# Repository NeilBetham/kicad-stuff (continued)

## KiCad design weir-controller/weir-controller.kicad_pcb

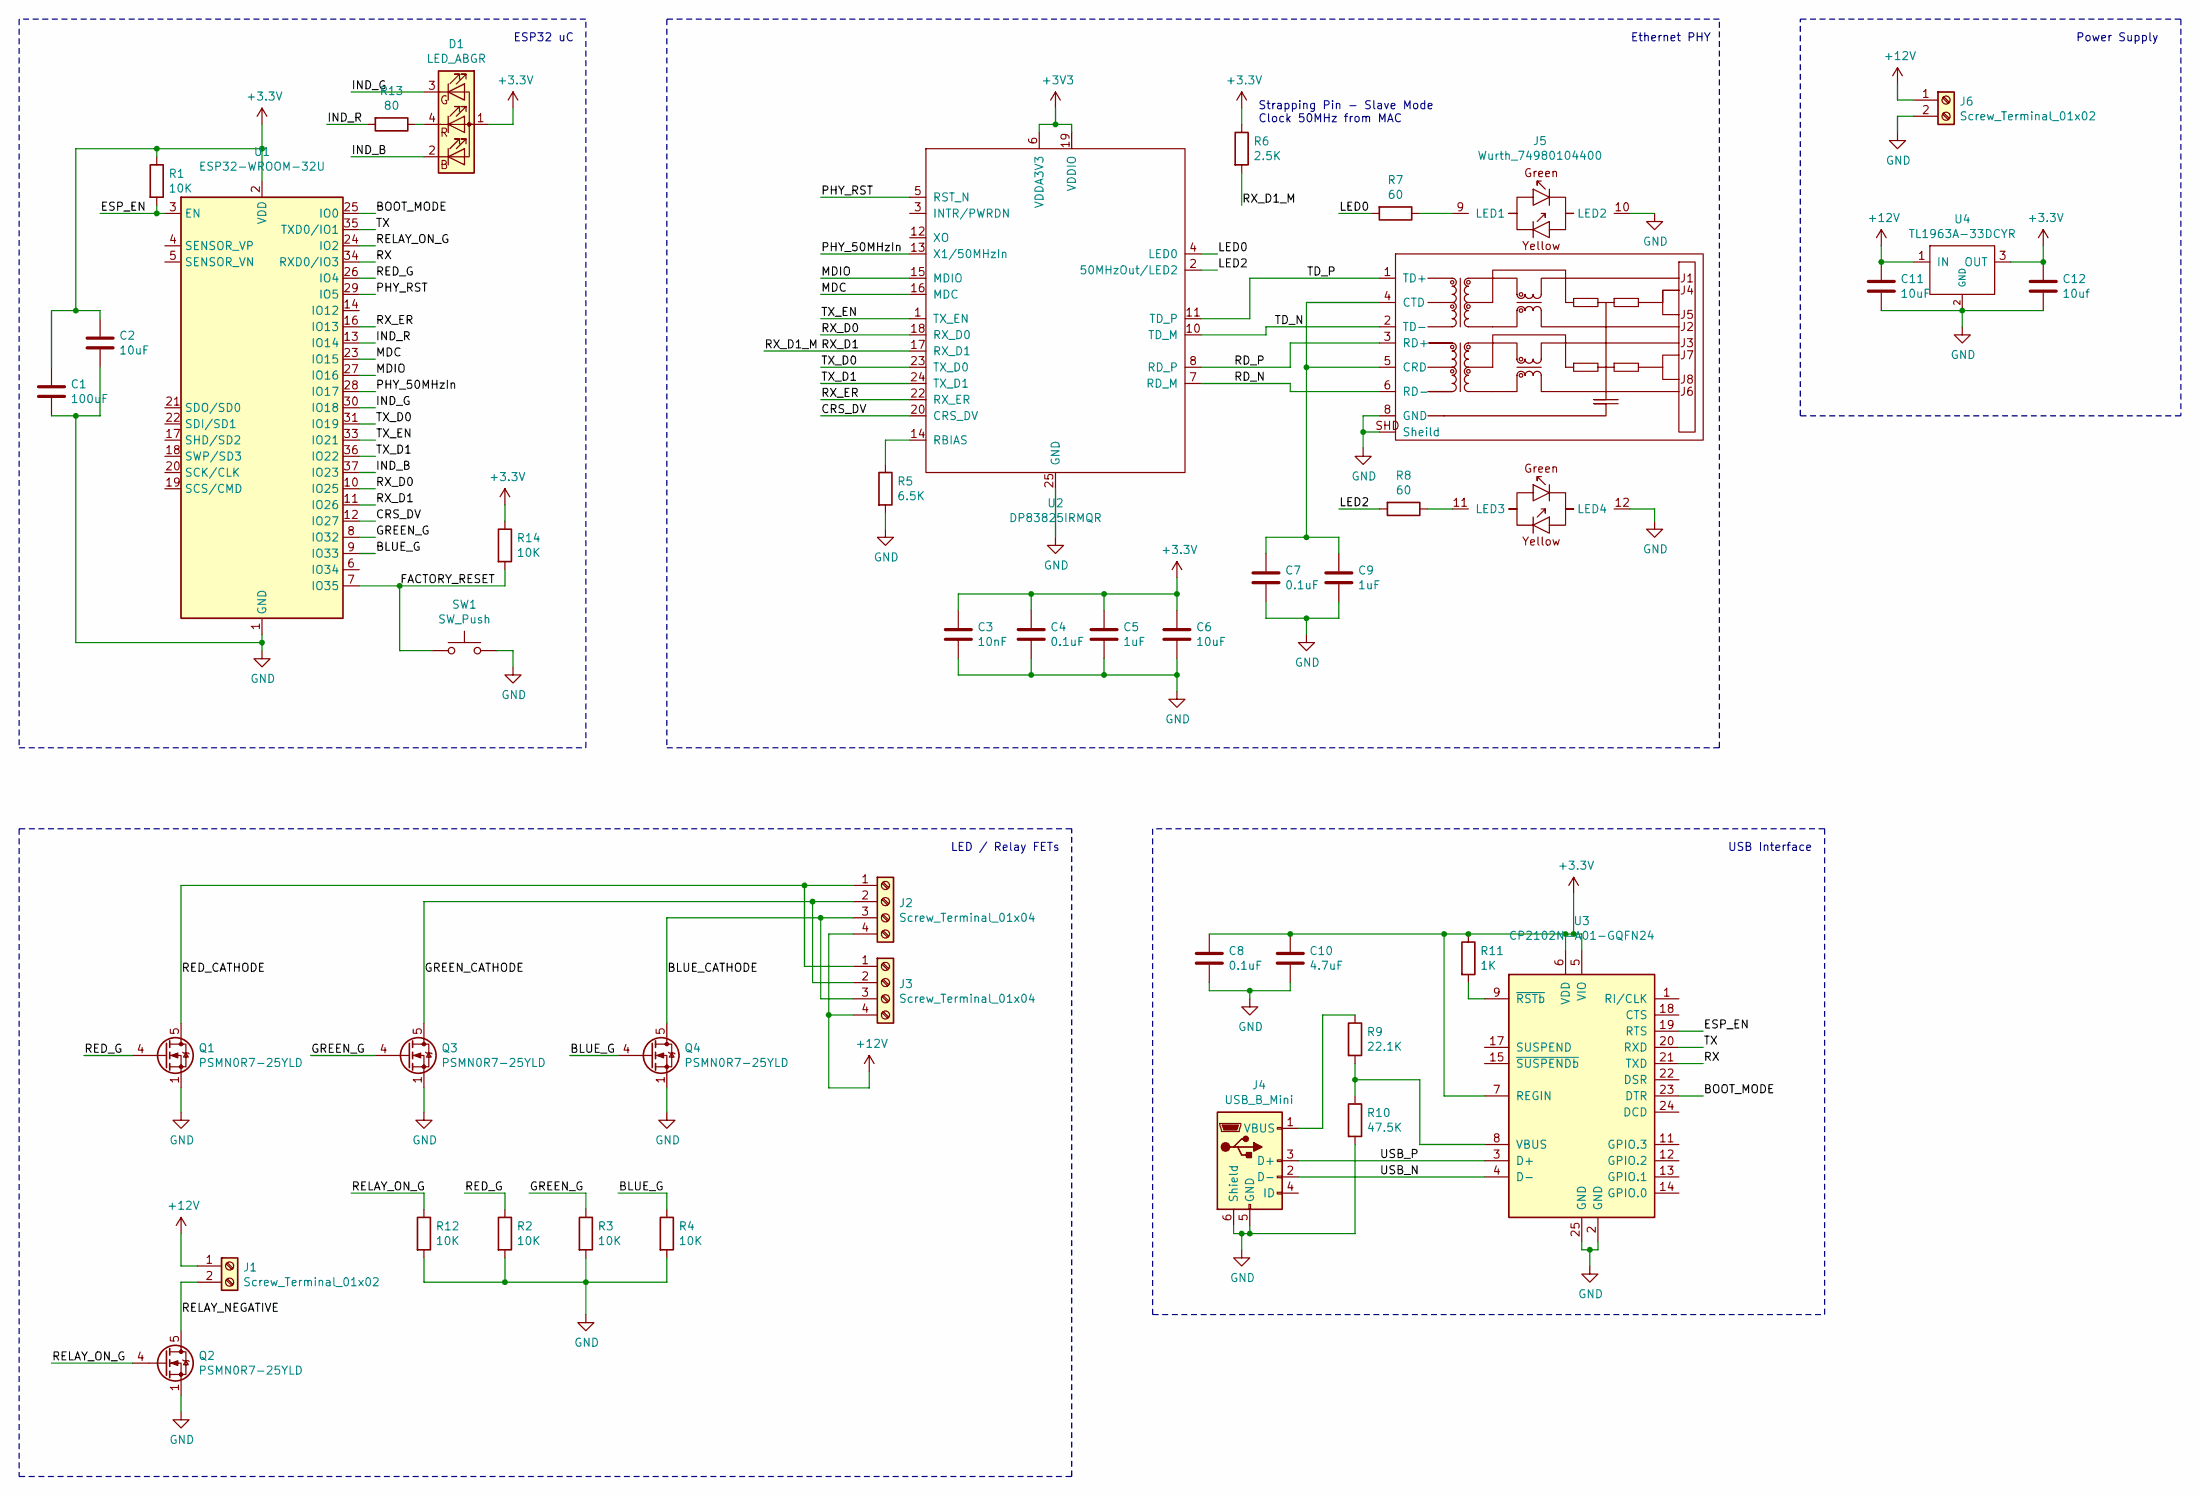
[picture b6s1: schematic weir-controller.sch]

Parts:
C1: 100uF; C_1206_3216Metric_Pad1.42x1.75mm_HandSolder
C2, C6, C11: 10uF; C_0805_2012Metric_Pad1.15x1.40mm_HandSolder
C3: 10nF; C_0805_2012Metric_Pad1.15x1.40mm_HandSolder
C4, C7, C8: 0.1uF; C_0805_2012Metric_Pad1.15x1.40mm_HandSolder
C5, C9: 1uF; C_0805_2012Metric_Pad1.15x1.40mm_HandSolder
C10: 4.7uF; C_0805_2012Metric_Pad1.15x1.40mm_HandSolder
C12: 10uf; C_0805_2012Metric_Pad1.15x1.40mm_HandSolder
D1: LED_ABGR; LED_Cree-PLCC4_2x2mm_CW
J1: Screw_Terminal_01x02; PhoenixContact_PTSA_2Pin
J2, J3: Screw_Terminal_01x04; PhoenixContact PTSA 4Pin
J4: USB_B_Mini; 54819-0589
J5: Wurth_74980104400
J6: Screw_Terminal_01x02; PhoenixContact_PTSA_2PIN_8A
Q1, Q2, Q3, Q4: PSMN0R7-25YLD; LFPAK56
R1, R2, R3, R4, R12: 10K; R_0805_2012Metric_Pad1.15x1.40mm_HandSolder
R5: 6.5K; R_0805_2012Metric_Pad1.15x1.40mm_HandSolder
R6: 2.5K; R_0805_2012Metric_Pad1.15x1.40mm_HandSolder
R7, R8: 60; R_0805_2012Metric_Pad1.15x1.40mm_HandSolder
R9: 22.1K; R_0805_2012Metric_Pad1.15x1.40mm_HandSolder
R10: 47.5K; R_0805_2012Metric_Pad1.15x1.40mm_HandSolder
R11: 1K; R_0805_2012Metric_Pad1.15x1.40mm_HandSolder
R13: 80; R_0805_2012Metric_Pad1.15x1.40mm_HandSolder
R14: 10K; R_0805_2012Metric_Pad1.20x1.40mm_HandSolder
SW1: SW_Push; PTS636
U1: ESP32-WROOM-32U
U2: DP83825IRMQR; TI_RMQ0024A
U3: CP2102N-A01-GQFN24; QFN-24-1EP_4x4mm_P0.5mm_EP2.6x2.6mm_ThermalVias
U4: TL1963A-33DCYR; SOT-223-3_TabPin2

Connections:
+12V: C11.1, J1.1, J2.4, J3.4, J6.1, U4.1 (IN)
/BLUE_CATHODE: J2.3, J3.3, Q4.5 (D)
/BLUE_G: Q4.4 (G), R4.1, U1.9 (IO33)
/BOOT_MODE: U1.25 (IO0), U3.23 (DTR)
/CRS_DV: U1.12 (IO27), U2.20 (CRS_DV)
/ESP_EN: R1.2, U1.3 (EN), U3.19 (RTS)
/FACTORY_RESET: R14.2, SW1.1, U1.7 (IO35)
/GREEN_CATHODE: J2.2, J3.2, Q3.5 (D)
/GREEN_G: Q3.4 (G), R3.1, U1.8 (IO32)
/IND_B: D1.2 (BK), U1.37 (IO23)
/IND_G: D1.3 (GK), U1.30 (IO18)
/IND_R: R13.2, U1.13 (IO14)
/LED0: R7.2, U2.4 (LED0)
/LED2: R8.2, U2.2 (50MHzOut/LED2)
/MDC: U1.23 (IO15), U2.16 (MDC)
/MDIO: U1.27 (IO16), U2.15 (MDIO)
/PHY_50MHzIn: U1.28 (IO17), U2.13 (X1/50MHzIn)
/PHY_RST: U1.29 (IO5), U2.5 (RST_N)
/RD_N: J5.6 (RD-), U2.7 (RD_M)
/RD_P: J5.3 (RD+), U2.8 (RD_P)
/RED_CATHODE: J2.1, J3.1, Q1.5 (D)
/RED_G: Q1.4 (G), R2.1, U1.26 (IO4)
/RELAY_NEGATIVE: J1.2, Q2.5 (D)
/RELAY_ON_G: Q2.4 (G), R12.1, U1.24 (IO2)
/RX: U1.34 (RXD0/IO3), U3.21 (TXD)
/RX_D0: U1.10 (IO25), U2.18 (RX_D0)
/RX_D1: R6.2, U1.11 (IO26), U2.17 (RX_D1)
/RX_ER: U1.16 (IO13), U2.22 (RX_ER)
/TD_N: J5.2 (TD-), U2.10 (TD_M)
/TD_P: J5.1 (TD+), U2.11 (TD_P)
/TX: U1.35 (TXD0/IO1), U3.20 (RXD)
/TX_D0: U1.31 (IO19), U2.23 (TX_D0)
/TX_D1: U1.36 (IO22), U2.24 (TX_D1)
/TX_EN: U1.33 (IO21), U2.1 (TX_EN)
/USB_N: J4.2 (D-), U3.4 (D-)
/USB_P: J4.3 (D+), U3.3 (D+)
GND: C1.2, C2.2, C3.2, C4.2, C5.2, C6.2, C7.2, C8.2, C9.2, C10.2, C11.2, C12.2, J4.5 (GND), J4.6 (Shield), J5.8 (GND), J5.10 (LED2), J5.12 (LED4), J5.SHD (Sheild), J6.2, Q1.1 (S), Q1.2 (S), Q1.3 (S), Q2.1 (S), Q2.2 (S), Q2.3 (S), Q3.1 (S), Q3.2 (S), Q3.3 (S), Q4.1 (S), Q4.2 (S), Q4.3 (S), R2.2, R3.2, R4.2, R5.2, R10.2, R12.2, SW1.2, U1.1 (GND), U1.15 (GND), U1.38 (GND), U1.39 (GND), U2.9 (GND), U2.21 (GND), U2.25 (GND), U3.2 (GND), U3.25 (GND), U4.2 (GND)
unnamed: C7.1, C9.1, J5.4 (CTD), J5.5 (CRD)
unnamed: D1.4 (RK), R13.1
unnamed: J4.1 (VBUS), R9.1
unnamed: J5.9 (LED1), R7.1
unnamed: J5.11 (LED3), R8.1
unnamed: R5.1, U2.14 (RBIAS)
unnamed: R9.2, R10.1, U3.8 (VBUS)
unnamed: R11.2, U3.9 (~RSTb)

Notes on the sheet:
Power Supply
USB Interface
LED / Relay FETs
Strapping Pin - Slave Mode Clock 50MHz from MAC
Ethernet PHY
ESP32 uC

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
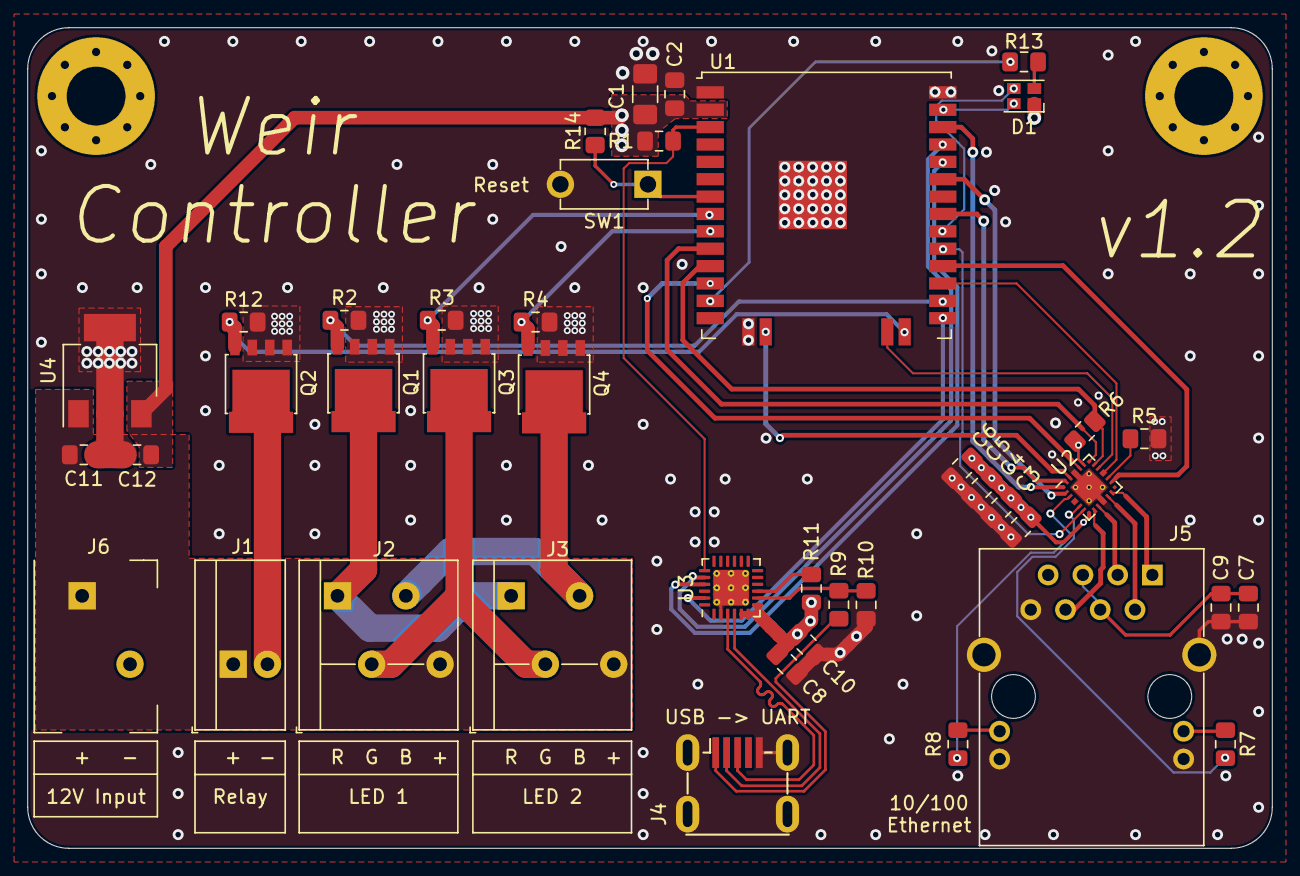
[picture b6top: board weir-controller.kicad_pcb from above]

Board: 4 copper layers, 91.0 x 60.0 mm, 42 parts (0 on the bottom side), 46 nets.

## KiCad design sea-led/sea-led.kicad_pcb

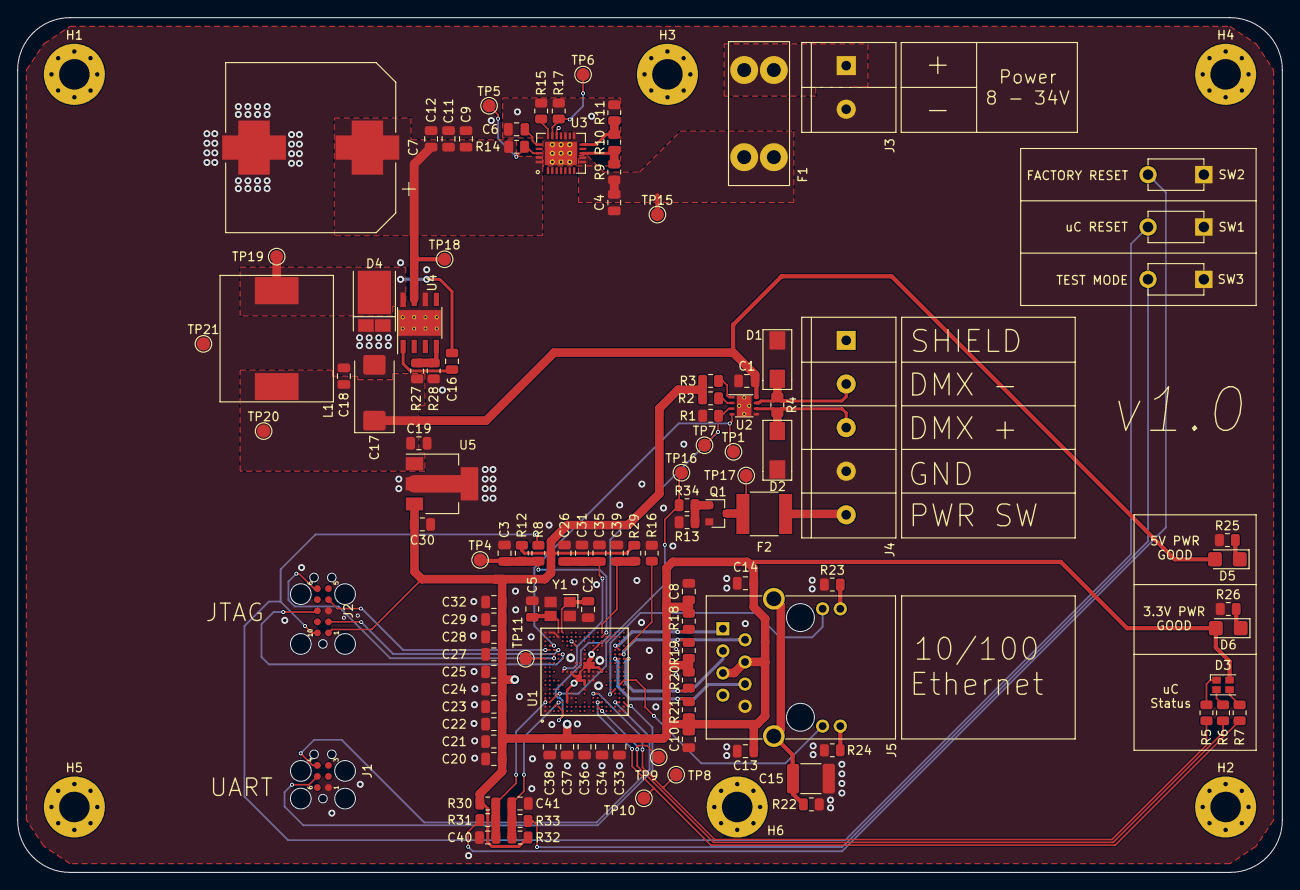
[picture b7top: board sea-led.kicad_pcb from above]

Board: 4 copper layers, 145.0 x 98.0 mm, 121 parts (0 on the bottom side), 61 nets.

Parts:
C1, C3, C8, C10, C13, C14, C21, C22, C23, C24, C25, C27, C28, C29, C32, C33, C34, C35, C36, C37, C38, C39, C40, C41: 0.1uF; C_0805_2012Metric
C2, C5: 8pF; C_0805_2012Metric
C4, C20, C31: 1uF; C_0805_2012Metric
C6: 5.5uF; C_0805_2012Metric
C7: 2200uF; Panasonic-Electrolytic-K16
C9, C11, C12: 4.7uF; C_0805_2012Metric
C15: 4700pF 2kV; C_1812_4532Metric
C16, C18: 0.01uF; C_0805_2012Metric
C17: 330uF; CP_EIA-7343-30_AVX-N_Pad2.25x2.55mm_HandSolder
C19, C30: 10uF; C_0805_2012Metric
C26: 2.2uF; C_0805_2012Metric
D1, D2: SMAJ30CA
D3: LED_ABGR; LED_Cree-PLCC4_2x2mm_CW
D4: PMEG045V100EPD; CFP15
D5: BLUE - HSMN-C150; LED_1206_3216Metric_Castellated
D6: GREEN - HSMM-C150; LED_1206_3216Metric_Castellated
F1: Keystone - 3568; Keystone-3568
F2: 2016L075/60MR; 2016L075_60MR
H1, H2, H3, H4, H5, H6: MountingHole; MountingHole_3.5mm_Pad_Via
J1: TC2030-UART; TC2030-IDC-FP
J2: TC-2050-Cortex-JTAG; TC2050-IDC-FP
J3: Screw_Terminal_01x02; PhoenixContact-PTS-1_5-2POS-1703084
J4: Screw_Terminal_01x05; PhoenixContact-PTS-1_5-5POS-1792892
J5: Wurth_74980104400
L1: 15uH SRP1265A-150M; SRP1265A-150M
Q1: FDN5630; SOT-23
R1, R2, R3, R12, R13, R14, R27, R30, R32: 10k; R_0805_2012Metric
R4: 120; R_0805_2012Metric
R5, R6, R7, R8, R31, R33, R34: 100; R_0805_2012Metric
R9: 706k; R_0805_2012Metric
R10: 145k; R_0805_2012Metric
R11: 30.1k; R_0805_2012Metric
R15: 2.4k; R_0805_2012Metric
R16: 4.87k; R_0805_2012Metric
R17: 6.6k; R_0805_2012Metric
R18, R19, R20, R21: 49.9; R_0805_2012Metric
R22: 1M; R_0805_2012Metric
R23, R24, R25, R26: 330; R_0805_2012Metric
R28: 3.16k; R_0805_2012Metric
R29: 51; R_0805_2012Metric
SW1, SW2, SW3: SW_Push; PTS636
TP1, TP4, TP5, TP6, TP7, TP8, TP9, TP10, TP11, TP15, TP16, TP17, TP18, TP19, TP20, TP21: TestPoint; TestPoint_Pad_D1.5mm
U1: TM4C129ENCZADI3R
U2: THVD2450; VSON-8
U3: TPS2660; VQFN-24
U4: TPS5450; PowerPAD-SOIC-8
U5: TL1963A-33DCYR; SOT-223-3_TabPin2
Y1: LFXTAL071758Cutt; LFXTAL071758CUTT

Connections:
+3V3: C8.1, C10.1, C13.1, C14.1, C20.1, C21.1, C22.1, C23.1, C24.1, C25.1, C27.1, C28.1, C29.1, C30.1, C32.1, C33.1, C34.1, C36.1, C37.1, C38.1, D3.2, D6.2, J2.1, J5.4, J5.5, R2.1, R3.1, R12.1, R18.1, R19.1, R20.1, R21.1, R29.1, R30.1, R32.1, U1.F3, U1.F4, U1.G10, U1.H9, U1.J8, U1.J9, U1.J10, U1.K7, U1.K8, U1.K11, U1.K12, U1.L10, U1.L11, U1.L12, U1.M11, U1.M12, U1.N16, U1.P10, U1.P17, U5.3
+5V: C1.1, C17.1, C18.1, C19.1, D5.2, L1.2, R27.1, TP20.1, U2.8, U5.1
+12V: C7.1, C9.1, C11.1, C12.1, R14.1, TP18.1, U3.23, U3.24, U4.7
+BATT: F1.2, J3.1
/DIVSCLK: TP11.1, U1.A13
/DMX_N: D1.2, J4.2, R4.1, U2.7
/DMX_P: D2.1, J4.3, R4.2, U2.6
/DMX_TX: TP1.1, U1.B16, U2.4
/DMX_TX_EN: R1.1, TP7.1, U1.D2, U2.3
/ETH_LED1: J5.9, U1.U6
/ETH_LED2: J5.10, R23.2
/ETH_LED3: J5.11, U1.V7
/ETH_LED4: J5.12, R24.1
/ETH_RX_N: J5.6, R21.2, U1.V13
/ETH_RX_P: J5.3, R20.2, U1.W13
/ETH_TX_N: J5.2, R19.2, U1.V14
/ETH_TX_P: J5.1, R18.2, U1.V15
/FACTORY_RESET: C40.1, R30.2, R31.1, U1.A4
/IND_B: R7.1, TP10.1, U1.P3
/IND_G: R6.1, TP9.1, U1.N2
/IND_R: R5.1, TP8.1, U1.N5
/JTAG_RESET: J2.10, R8.2, SW1.2
/JTAG_TCK: J2.4, U1.B15
/JTAG_TDI: J2.8, U1.D14
/JTAG_TDO: J2.6, U1.C14
/JTAG_TMS: J2.2, U1.C15
/PWR_SW: F2.1, J4.5
/PWR_SW_CTL: R34.2, TP16.1, U1.B3
/TEST_MODE: C41.1, R32.2, R33.1, U1.C2
/UART_RX: J1.4, U1.V3
/UART_TX: J1.5, U1.W3
GND: C1.2, C2.2, C3.2, C4.2, C5.2, C7.2, C8.2, C9.2, C10.2, C11.2, C12.2, C13.2, C14.2, C15.2, C17.2, C18.2, C19.2, C20.2, C21.2, C22.2, C23.2, C24.2, C25.2, C26.2, C27.2, C28.2, C29.2, C30.2, C31.2, C32.2, C33.2, C34.2, C35.2, C36.2, C37.2, C38.2, C39.2, C40.2, C41.2, D1.1, D2.2, D4.2, J1.1, J2.3, J3.2, J4.4, J5.8, Q1.2, R1.2, R13.2, R16.2, R22.2, R23.1, R24.2, R25.1, R26.1, R28.2, SW1.1, SW2.1, SW3.1, TP21.1, U1.A1, U1.A2, U1.A18, U1.A19, U1.B1, U1.B19, U1.D18, U1.F10, U1.G4, U1.G5, U1.H10, U1.H11, U1.H12, U1.J11, U1.J12, U1.K6, U1.K9, U1.K10, U1.K13, U1.K14, U1.L8, U1.L9, U1.M8, U1.M9, U1.M10, U1.N10, U1.P16, U1.R17, U1.R18, U1.T18, U1.U18, U1.V1, U1.W1, U1.W2, U2.5, U2.9, U3.17, U4.6, U4.9, U5.2, Y1.2, Y1.4
unnamed: C2.1, U1.E19, Y1.1
unnamed: C3.1, R8.1, R12.2, TP4.1, U1.P18
unnamed: C4.1, F1.1, R9.1, TP15.1, U3.8, U3.9
unnamed: C5.1, U1.D19, Y1.3
unnamed: C6.1, U3.20
unnamed: C6.2, R11.2, R15.2, R17.2, U3.13, U3.15, U3.25
unnamed: C15.1, J5.SHD, R22.1
unnamed: C16.1, D4.1, L1.1, TP19.1, U4.8
unnamed: C16.2, U4.1
unnamed: C26.1, C31.1, C35.1, U1.E10, U1.H16
unnamed: C39.1, R29.2, U1.P19
unnamed: D3.1, R5.2
unnamed: D3.3, R7.2
unnamed: D3.4, R6.2
unnamed: D5.1, R25.2
unnamed: D6.1, R26.2
unnamed: F2.2, Q1.3, TP17.1
unnamed: Q1.1, R13.1, R34.1
unnamed: R2.2, U2.2
unnamed: R3.2, U2.1
unnamed: R9.2, R10.1, U3.10
unnamed: R10.2, R11.1, U3.12
unnamed: R14.2, TP5.1, U3.22
unnamed: R15.1, U3.19
unnamed: R16.1, U1.W15
unnamed: R17.1, TP6.1, U3.18
unnamed: R27.2, R28.1, U4.4
unnamed: R31.2, SW2.2
unnamed: R33.2, SW3.2

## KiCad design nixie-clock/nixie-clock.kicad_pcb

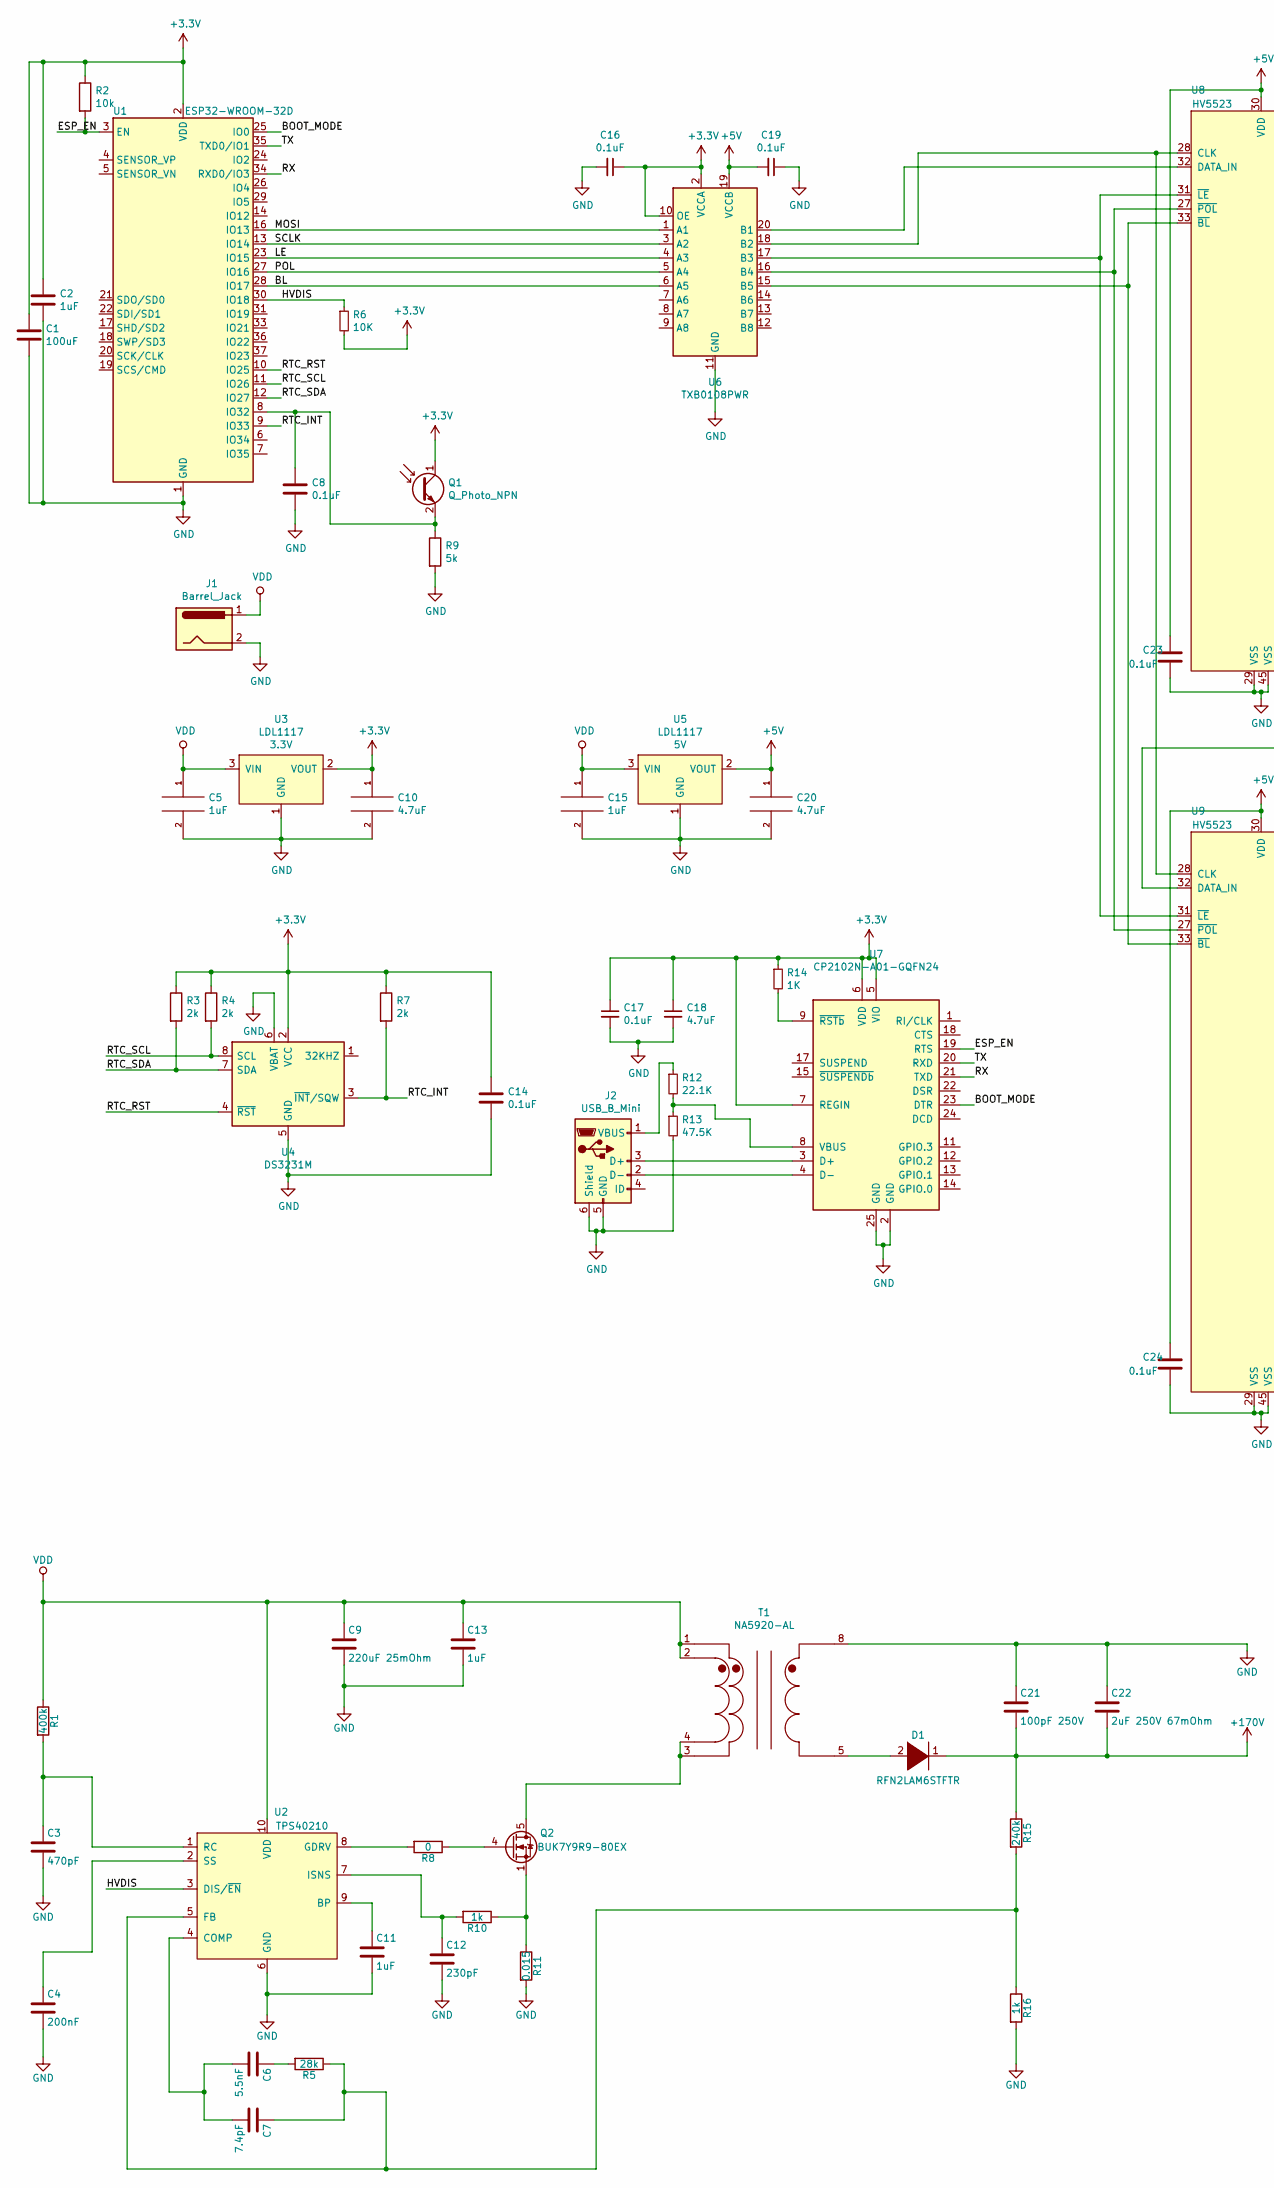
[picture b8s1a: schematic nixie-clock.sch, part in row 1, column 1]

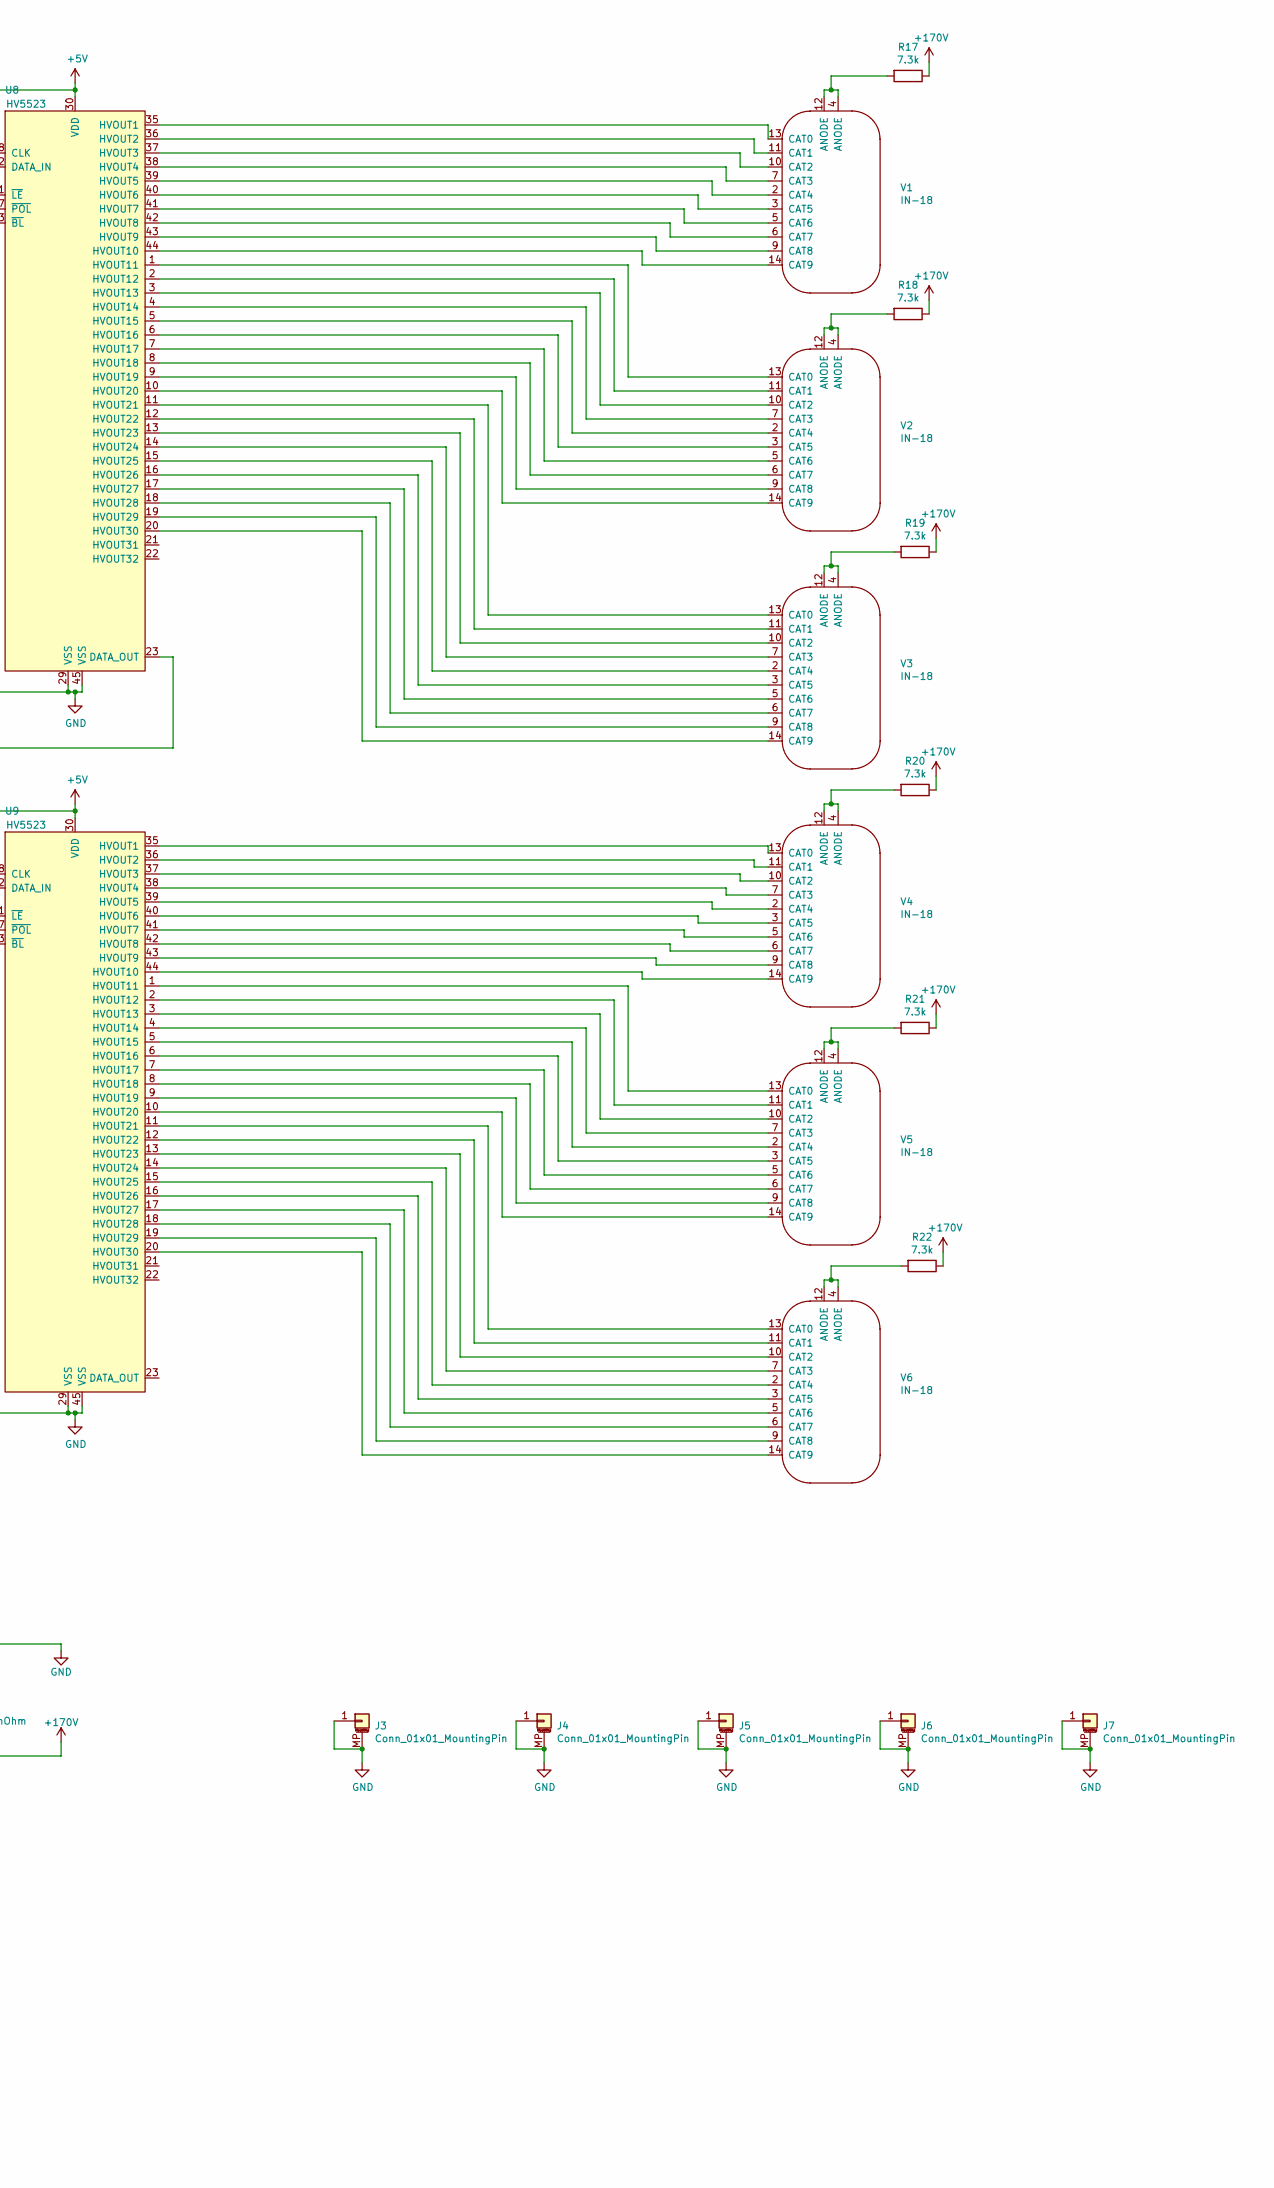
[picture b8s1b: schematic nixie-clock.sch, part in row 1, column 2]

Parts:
C1: 100uF; C_1206_3216Metric_Pad1.42x1.75mm_HandSolder
C2, C5, C11, C13, C15: 1uF; C_0805_2012Metric_Pad1.15x1.40mm_HandSolder
C3: 470pF; C_0805_2012Metric_Pad1.15x1.40mm_HandSolder
C4: 200nF; C_0805_2012Metric_Pad1.15x1.40mm_HandSolder
C6: 5.5nF; C_0805_2012Metric_Pad1.15x1.40mm_HandSolder
C7: 7.4pF; C_0805_2012Metric_Pad1.15x1.40mm_HandSolder
C8, C14, C16, C17, C19, C23, C24: 0.1uF; C_0805_2012Metric_Pad1.15x1.40mm_HandSolder
C9: 220uF 25mOhm; C_2816_7142Metric_Pad3.20x4.45mm_HandSolder; Part Number TPME227K016R0025
C10, C18, C20: 4.7uF; C_0805_2012Metric_Pad1.15x1.40mm_HandSolder
C12: 230pF; C_0805_2012Metric_Pad1.15x1.40mm_HandSolder
C21: 100pF 250V; C_0805_2012Metric_Pad1.15x1.40mm_HandSolder
C22: 2uF 250V 67mOhm; C_2220_5650Metric_Pad1.97x5.40mm_HandSolder
D1: RFN2LAM6STFTR; SOD-128-2
J1: Barrel_Jack; BarrelJack_CUI_PJ-102AH_Horizontal
J2: USB_B_Mini; 54819-0589
J3, J4, J5, J6, J7: Conn_01x01_MountingPin; 4MM_Mounting_Hole
Q1: Q_Photo_NPN; R_1206_3216Metric_Pad1.42x1.75mm_HandSolder; Part Number TEMT6000X01
Q2: BUK7Y9R9-80EX; LFPAK56
R1: 400k; R_0805_2012Metric_Pad1.15x1.40mm_HandSolder
R2: 10k; R_0805_2012Metric_Pad1.15x1.40mm_HandSolder
R3, R4, R7: 2k; R_0805_2012Metric_Pad1.15x1.40mm_HandSolder
R5: 28k; R_0805_2012Metric_Pad1.15x1.40mm_HandSolder
R6: 10K; R_0805_2012Metric_Pad1.15x1.40mm_HandSolder
R8: 0; R_0805_2012Metric_Pad1.15x1.40mm_HandSolder
R9: 5k; C_0805_2012Metric_Pad1.15x1.40mm_HandSolder
R10: 1k; C_0805_2012Metric_Pad1.15x1.40mm_HandSolder
R11: 0.015; R_GMR_100
R12: 22.1K; R_0805_2012Metric_Pad1.15x1.40mm_HandSolder
R13: 47.5K; R_0805_2012Metric_Pad1.15x1.40mm_HandSolder
R14: 1K; R_0805_2012Metric_Pad1.15x1.40mm_HandSolder
R15: 240k; R_0805_2012Metric_Pad1.15x1.40mm_HandSolder
R16: 1k; R_0805_2012Metric_Pad1.15x1.40mm_HandSolder
R17, R18, R19, R20, R21, R22: 7.3k; R_0805_2012Metric_Pad1.15x1.40mm_HandSolder
T1: NA5920-AL; NA6252-AL
U1: ESP32-WROOM-32D; ESP32-WROOM-32
U2: TPS40210; MSOP-10-1EP_3x3mm_P0.5mm_EP1.68x1.88mm
U3: LDL1117; SOT-223-3_TabPin2; Voltage 3.3V
U4: DS3231M; SOIC-8_3.9x4.9mm_P1.27mm
U5: LDL1117; SOT-223-3_TabPin2; Voltage 5V
U6: TXB0108PWR; TSSOP-20_4.4x6.5mm_P0.65mm
U7: CP2102N-A01-GQFN24; QFN-24-1EP_4x4mm_P0.5mm_EP2.6x2.6mm
U8, U9: HV5523; QFN-44-1EP_7x7mm_P0.5mm_EP5.15x5.15mm_ThermalVias
V1, V2, V3, V4, V5, V6: IN-18; IN-18 Socket

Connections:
+3V3: C1.1, C2.1, C10.1, C14.1, C16.1, C17.1, C18.1, Q1.1 (C), R2.1, R3.1, R4.1, R6.2, R7.1, R14.1, U1.2 (VDD), U3.2 (VOUT), U4.2 (VCC), U6.2 (VCCA), U6.10 (OE), U7.5 (VIO), U7.6 (VDD), U7.7 (REGIN)
+5V: C19.2, C20.1, C23.1, C24.1, U5.2 (VOUT), U6.19 (VCCB), U8.30 (VDD), U9.30 (VDD)
+170V: C21.2, C22.2, D1.1 (A), R15.1, R17.1, R18.1, R19.1, R20.1, R21.1, R22.1
/BL: U1.28 (IO17), U6.6 (A5)
/BOOT_MODE: U1.25 (IO0), U7.23 (DTR)
/ESP_EN: R2.2, U1.3 (EN), U7.19 (RTS)
/HVDIS: R6.1, U1.30 (IO18), U2.3 (DIS/~EN)
/LE: U1.23 (IO15), U6.4 (A3)
/MOSI: U1.16 (IO13), U6.1 (A1)
/POL: U1.27 (IO16), U6.5 (A4)
/RTC_INT: R7.2, U1.9 (IO33), U4.3 (~INT~/SQW)
/RTC_RST: U1.10 (IO25), U4.4 (~RST)
/RTC_SCL: R4.2, U1.11 (IO26), U4.8 (SCL)
/RTC_SDA: R3.2, U1.12 (IO27), U4.7 (SDA)
/RX: U1.34 (RXD0/IO3), U7.21 (TXD)
/SCLK: U1.13 (IO14), U6.3 (A2)
/TX: U1.35 (TXD0/IO1), U7.20 (RXD)
GND: C1.2, C2.2, C3.2, C4.2, C5.2, C8.2, C9.2, C10.2, C11.2, C12.2, C13.2, C14.2, C15.2, C16.2, C17.2, C18.2, C19.1, C20.2, C21.1, C22.1, C23.2, C24.2, J1.2, J2.5 (GND), J2.6 (Shield), J3.1, J3.MP (MountPin), J4.1, J4.MP (MountPin), J5.1, J5.MP (MountPin), J6.1, J6.MP (MountPin), J7.1, J7.MP (MountPin), R9.2, R11.2, R13.2, R16.2, T1.8, U1.1 (GND), U1.15 (GND), U1.38 (GND), U1.39 (GND), U2.6 (GND), U2.11 (GND), U3.1 (GND), U4.5 (GND), U4.6 (VBAT), U5.1 (GND), U6.11 (GND), U7.2 (GND), U7.25 (GND), U8.29 (VSS), U8.45 (VSS), U9.29 (VSS), U9.45 (VSS)
unnamed: C3.1, R1.2, U2.1 (RC)
unnamed: C4.1, U2.2 (SS)
unnamed: C6.1, R5.2
unnamed: C6.2, C7.2, U2.4 (COMP)
unnamed: C7.1, R5.1, R15.2, R16.1, U2.5 (FB)
unnamed: C8.1, Q1.2 (E), R9.1, U1.8 (IO32)
unnamed: C11.1, U2.9 (BP)
unnamed: C12.1, R10.2, U2.7 (ISNS)
unnamed: D1.2 (K), T1.5
unnamed: J2.1 (VBUS), R12.1
unnamed: J2.2 (D-), U7.4 (D-)
unnamed: J2.3 (D+), U7.3 (D+)
unnamed: Q2.1 (S), Q2.2 (S), Q2.3 (S), R10.1, R11.1
unnamed: Q2.4 (G), R8.1
unnamed: Q2.5 (D), T1.3, T1.4
unnamed: R8.2, U2.8 (GDRV)
unnamed: R12.2, R13.1, U7.8 (VBUS)
unnamed: R14.2, U7.9 (~RSTb)
unnamed: R17.2, V1.4 (ANODE), V1.12 (ANODE)
unnamed: R18.2, V2.4 (ANODE), V2.12 (ANODE)
unnamed: R19.2, V3.4 (ANODE), V3.12 (ANODE)
unnamed: R20.2, V4.4 (ANODE), V4.12 (ANODE)
unnamed: R21.2, V5.4 (ANODE), V5.12 (ANODE)
unnamed: R22.2, V6.4 (ANODE), V6.12 (ANODE)
unnamed: U6.15 (B5), U8.33 (~BL), U9.33 (~BL)
unnamed: U6.16 (B4), U8.27 (~POL), U9.27 (~POL)
unnamed: U6.17 (B3), U8.31 (~LE), U9.31 (~LE)
unnamed: U6.18 (B2), U8.28 (CLK), U9.28 (CLK)
unnamed: U6.20 (B1), U8.32 (DATA_IN)
unnamed: U8.1 (HVOUT11), V2.13 (CAT0)
unnamed: U8.2 (HVOUT12), V2.11 (CAT1)
unnamed: U8.3 (HVOUT13), V2.10 (CAT2)
unnamed: U8.4 (HVOUT14), V2.7 (CAT3)
unnamed: U8.5 (HVOUT15), V2.2 (CAT4)
unnamed: U8.6 (HVOUT16), V2.3 (CAT5)
unnamed: U8.7 (HVOUT17), V2.5 (CAT6)
unnamed: U8.8 (HVOUT18), V2.6 (CAT7)
unnamed: U8.9 (HVOUT19), V2.9 (CAT8)
unnamed: U8.10 (HVOUT20), V2.14 (CAT9)
unnamed: U8.11 (HVOUT21), V3.13 (CAT0)
unnamed: U8.12 (HVOUT22), V3.11 (CAT1)
unnamed: U8.13 (HVOUT23), V3.10 (CAT2)
unnamed: U8.14 (HVOUT24), V3.7 (CAT3)
unnamed: U8.15 (HVOUT25), V3.2 (CAT4)
unnamed: U8.16 (HVOUT26), V3.3 (CAT5)
unnamed: U8.17 (HVOUT27), V3.5 (CAT6)
unnamed: U8.18 (HVOUT28), V3.6 (CAT7)
unnamed: U8.19 (HVOUT29), V3.9 (CAT8)
unnamed: U8.20 (HVOUT30), V3.14 (CAT9)
unnamed: U8.23 (DATA_OUT), U9.32 (DATA_IN)
unnamed: U8.35 (HVOUT1), V1.13 (CAT0)
unnamed: U8.36 (HVOUT2), V1.11 (CAT1)
unnamed: U8.37 (HVOUT3), V1.10 (CAT2)
unnamed: U8.38 (HVOUT4), V1.7 (CAT3)
unnamed: U8.39 (HVOUT5), V1.2 (CAT4)
unnamed: U8.40 (HVOUT6), V1.3 (CAT5)
unnamed: U8.41 (HVOUT7), V1.5 (CAT6)
unnamed: U8.42 (HVOUT8), V1.6 (CAT7)
unnamed: U8.43 (HVOUT9), V1.9 (CAT8)
unnamed: U8.44 (HVOUT10), V1.14 (CAT9)
unnamed: U9.1 (HVOUT11), V5.13 (CAT0)
unnamed: U9.2 (HVOUT12), V5.11 (CAT1)
unnamed: U9.3 (HVOUT13), V5.10 (CAT2)
unnamed: U9.4 (HVOUT14), V5.7 (CAT3)
unnamed: U9.5 (HVOUT15), V5.2 (CAT4)
unnamed: U9.6 (HVOUT16), V5.3 (CAT5)
unnamed: U9.7 (HVOUT17), V5.5 (CAT6)
unnamed: U9.8 (HVOUT18), V5.6 (CAT7)
unnamed: U9.9 (HVOUT19), V5.9 (CAT8)
unnamed: U9.10 (HVOUT20), V5.14 (CAT9)
unnamed: U9.11 (HVOUT21), V6.13 (CAT0)
unnamed: U9.12 (HVOUT22), V6.11 (CAT1)
unnamed: U9.13 (HVOUT23), V6.10 (CAT2)
unnamed: U9.14 (HVOUT24), V6.7 (CAT3)
unnamed: U9.15 (HVOUT25), V6.2 (CAT4)
unnamed: U9.16 (HVOUT26), V6.3 (CAT5)
unnamed: U9.17 (HVOUT27), V6.5 (CAT6)
unnamed: U9.18 (HVOUT28), V6.6 (CAT7)
unnamed: U9.19 (HVOUT29), V6.9 (CAT8)
unnamed: U9.20 (HVOUT30), V6.14 (CAT9)
unnamed: U9.35 (HVOUT1), V4.13 (CAT0)
unnamed: U9.36 (HVOUT2), V4.11 (CAT1)
unnamed: U9.37 (HVOUT3), V4.10 (CAT2)
unnamed: U9.38 (HVOUT4), V4.7 (CAT3)
unnamed: U9.39 (HVOUT5), V4.2 (CAT4)
unnamed: U9.40 (HVOUT6), V4.3 (CAT5)
unnamed: U9.41 (HVOUT7), V4.5 (CAT6)
unnamed: U9.42 (HVOUT8), V4.6 (CAT7)
unnamed: U9.43 (HVOUT9), V4.9 (CAT8)
unnamed: U9.44 (HVOUT10), V4.14 (CAT9)
VDD: C5.1, C9.1, C13.1, C15.1, J1.1, R1.1, T1.1, T1.2, U2.10 (VDD), U3.3 (VIN), U5.3 (VIN)

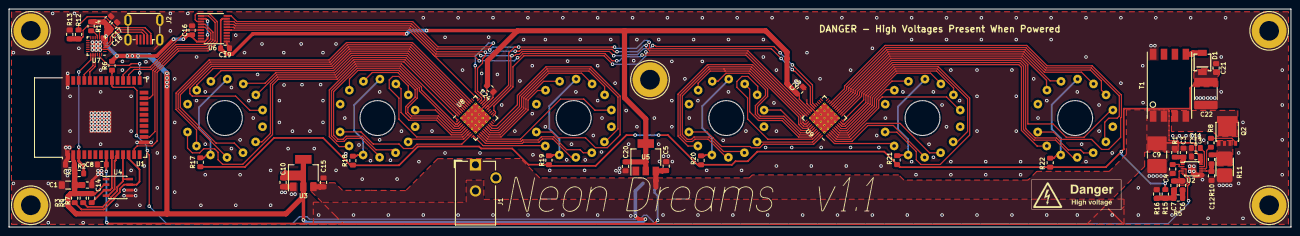
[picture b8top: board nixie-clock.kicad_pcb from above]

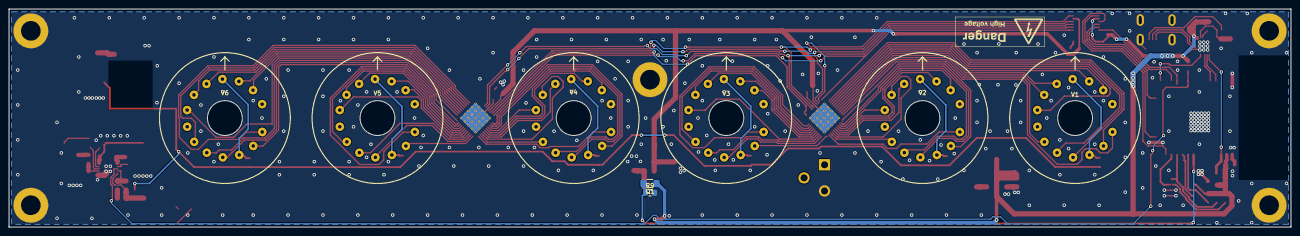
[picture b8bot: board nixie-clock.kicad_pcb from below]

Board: 2 copper layers, 294.0 x 50.0 mm, 72 parts (8 on the bottom side), 109 nets.

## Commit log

2015-08-24 keyboard ish
2015-08-27 lots of pcb work
2015-08-27 pcb layout updates
2015-08-30 Add stabs to big keys
2015-08-30 readme with handy links
2015-08-30 Stabilizers placed and spaced
2015-08-30 Added status LEDs but they can't be driven by the micro.
2015-08-30 LEDs added, but not placed
2018-12-27 Nixie Tube Clock WIP
2018-12-30 Added IN-18 Socket
2019-01-07 Move keyboard stuff to it's own folder
2019-01-10 Nixie Clock progress
2019-01-14 Add seprate project for HV supply validation
2019-01-14 More power supply work
2019-01-16 Initial spin of hv power supply test board
2019-01-17 Clock schematic draft finished
2019-01-18 Preliminary / rough board layout
2019-01-22 Top layer ground plane and stitching
2019-01-26 Fix overlapping refs
2019-01-27 Nixie Clock Fixes / Tweaks
    - Connect TPS40210 power pad to ground.
    - Exact board outlines
    - Remove refs from mounting holes
2019-02-05 Fix lots of layout issues in high voltage power supply
    1. Don't route power through bottom layer ground plane
    2. Make sure U1 grounding pad is connected
    3. Kelvin connections for current sense resistor
    4. Pour keepouts under transformer
    5. Keep voltage feedback divider near IC
2019-02-22 HV power supply works, swap tubes to other side of board
2019-03-04 Tweak couple things before sending to fab
2019-04-09 Fixes from v1.0
2019-04-09 Annotate remaining footprints
2019-04-11 Reroute everything affected by v1.1 changes
2019-04-11 Fix logo and version
2019-04-11 Add high voltage danger warnings
2019-04-23 Fix footprint in schematic
2020-04-13 Init weir controller project
2020-04-13 Parts for days
2020-04-15 Move libs, inital rev of weir controller
2020-04-17 Weir Controller v1.0
2020-04-17 Add paste gerber
2020-05-11 Fix a bunch of fuck ups
2020-06-12 Remove phy interrupt
2020-08-22 v1.1.1
2020-12-24 Try 4 layer for RMII trace impedance
2020-12-24 Tweak keepout
2021-01-13 Impedance match the MDI
2021-03-20 Project Updates
    Final ref of Weir Controller board. Starting Davis Receiver Board. The later only has the PoE power stage captured.
2021-03-21 Davis Receiver RF Trans Captured
2021-03-21 Davis Receiver Captures
    More capture for the Davis receiver.
2021-03-22 Davis Receiver Capture Complete
    Captured the rest of the Davis Receiver schematic. Captured all necessary footprints. Assigned all footprints. Onto PCB layout...
2021-03-24 Davis Receiver v1.0
2021-04-14 Davis Receiver v1.1
2021-04-22 Updates and new projects
2021-04-24 Lots of footprint updates
2021-05-22 Sea LED Routing Complete
2021-06-20 Updates to DavisReceiver
2021-11-15 Davis RX Updates
2022-05-27 Davis RX and Weir Controller changes
2022-06-04 USB C 12/5V Supply Progress
2022-06-06 Part updates
2022-06-08 WIP on USB-C power supply
2022-06-18 Schematic first pass for pd supply
2022-08-05 Progress on USB C Power Supply
2022-08-07 Finished USB C PD Supply Layout
2022-09-15 USB C PD Power Supply Updates
2022-10-16 Cleanup + bugfixes
2022-10-16 WIP on Square Dishy PD PS
2022-10-16 Ignore backups
2023-01-01 Dishy supply rev 1 complete
2023-01-01 Fix silk
2023-01-01 Fixes
2023-01-01 Tweaks
2023-01-25 Welp
2023-02-13 Starlink PD Updates
2023-02-19 Updates to starlink PD design
2023-02-20 Finish layout
2023-02-20 Update Version
2023-04-05 Updated Starlink PD supply
    Fixed issues with pfet biasing.
    Switched to a synchronous convertor.
    Fixed nfet pinout.
    Fixed paste under micro
2023-07-24 Start on e-paper humidity disply
2023-09-03 Add projects
2023-09-04 Part selections
2023-09-10 More WIP
2023-10-22 New high current e-fuse
2023-10-22 Breakup design into smaller hierarchical sheets
2023-10-22 Assign the bulk of parts, some passives still need custom footprints.
2023-12-23 Vac progress
2023-12-27 bilge vac 1v0
2024-01-01 e-paper-hum-wip
2024-02-11 E Paper Hum WIP
2024-02-15 Hum WIP
2024-02-15 E Paper Hum Layout Complete
2024-02-18 Fix dumb bugs
